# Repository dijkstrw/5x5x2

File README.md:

5x5x2 aka Orochi!
=================

This is a 5x5 Cherry mx matrix with hotswap Kailh sockets based my own
firmware for the STM32F1 with libopencm3. The project contains
firmware, schematics and a board layout in kicad.

Features you expect given the above picture:
- bios boot and nkro keyboards, using usb keyboard scancodes
- system and consumer codes
- mouse events
- usb serial interface for configuration
- 8 sk68xx background leds on the bottom board
- 25 sk68xx underglow leds on the top board
- rotary encoder

Advanced features:
- adjustable speed macrokeys to e.g. emit passwords
- all leds individually addressable, colorchord support
- leds can light on e.g. volume or desktop changes
- configuration can be adjusted and flashed in userflash
- and an automouse that can simulate fast clicking

More pictures of the board and the development dongle are
[here](docs/IMAGES.md). If you want to build this yourself see
[building](docs/BUILDING.md). Interactive bom is
[here](https://glcdn.githack.com/dijkstrw/5x5x2/-/raw/30abe2597a5d5bfca67bad37a444652a956d1f03/schematic/bom/ibom.html).

Default firmware / my usecase
-----------------------------

This is my macropad; it contains three layers:

- X workspace layer, select workspace number, move about in VLC, start
  apps, compose key, quick jump to password layer and a number of app
  starting keys. Rotary dial controls system volume. Rotary press
  mutes/unmutes.

  Rgbleds show sound volume, current workspace / screen and active
  layer.

- numeric keypad, for when tkl is not enough

- macrokeys layer

Features
========

Keyboards
---------

The board provides 3 types of keyboards via different usb
endpoints.

1. The first is the usb standard bios keyboard definition, which
   allows the keyboard also to emit key codes to hosts with limited
   usb hid support. (This used to be the case in <2015 style bioses,
   hence the name.)

2. The second keyboard is a n-key-rollover, which exposes a keyboard
   that allows 224 usb keyboard scancodes to be pressed
   simultaneously. Also, because we do not need to adhere to the bios
   boot standard, this endpoint's interval can set much lower = it
   types much faster.

3. The third keyboard can emit so called consumer and system
   codes. Example consumer key codes are PLAY, PAUSE, but also MARK,
   CLEARMARK, REPEATFROMMARK. So everything the typical multimedia
   keys emit and then some.

Mouse
-----

Operate the rodent from your keyboard! There is support for x, y, 5
buttons and a vertical and horizontal scrollwheel action.

Serial
------

The board exposes a serial port for logging and
configuration. Configuration is done using commands, with these
general rules:

- Commands with lowercase letters request configuration information

- Commands with capital letters set configuration

- Arguments often are two hexadecimal digits long; e.g. ``00``,
  ``12``, ``fa``. If more digits are required, this is denoted in the
  argument specification by a colon, like so ``<argument:4>``.

The available commands are:

    ?  - show a terse description of available commands.

    i  - show usb info strings; contains the git-describe tag of the
         current firmware.

    d  - dump configuration of a named subsystem, see below.
    dg - dump the keymap light group
    dk - dump the keymap
    dp - dump the palette
    dr - dump the rotary configuration

    B  - set the bottom set of 8 leds (backlight) to custom rgb values.
         Takes a RGB argument of the form <rgb:6> times 8 for all leds.

    C  - set the top set of 25 leds (frontlight) to custom rgb values.
         Takes a RGB argument of the form <rgb:6> times 25 for all leds.

    D  - tell keyboard about an event that can be translated into a rgb
         light event, see below.
    DD - <screen><display> set current desktop display
    DM - <mute>            set sound output mute status
    DR - <mute>            set sound input/record mute
    DV - <volume:4>        set sound volume
         See config directory for a program that emits these events to the
         keyboard.

    G  - set light map for a key, takes argument of the form
         <layer><row><column><value>

    I  - set the rgb light intensity.

    K  - redefine a key in the keymap, takes argument of the form
         <layer><row><column><type><arg1><arg2><arg3>

    A  - clear all macro keys.

    M  - define one macro key, takes an argument of the form
         <number><oftenusedstring>. The number is a two hexdigits, the
         string can be upto 32 7-bit ascii chars long and is terminated
         with a newline.

    N  - set keyboard mode to <argument>; 00 for bios and 01 for nkro.
         Default is bios.

    P  - set palette color, takes arguments
         <number><hue:4><saturation><value>

    R  - redefine the rotary command, takes a argument of
         the form <layer><direction><type><arg1><arg2><arg3>

    L  - load configuration from flash

    S  - save configuration to flash

    Z  - clear the configration flash, revert to "factory" keymap at
         next powerup.

Command interpretation starts after receiving a newline.

Light events
------------

The keyboard will show desktop events as rgbled changes. This works in
a number of steps:

- There is a host program that connects to the serial port, monitors
  sound and workspace changes and communicates that back to the
  keyboard. The program can be found in
  [susanoo.py](config/susanoo.py). Note that workspace changes sent
  via a fifo using the desktop manager and
  [configuration](config/keys_orochi.lua).

- Incoming events are mapped to be shown on particular leds using the
  lightmap command.

- The events all have their own displays:

         B - backlight    - slow rainbow easing
         D - desktop      - desktop display mapped over palette
         L - layer        - layer mapped over palette
         m - macro        - if macro active, else backlight
         M - sound mute   - different colors for mute status
         V - volume       - volume mapped to color

Palette
-------

Colors in easings are assigned using a color index in the palette. The
default palette strives for a selection of colors that are visually
distinct from another.

The rotary action forward, backward and backlight colors have fixed
indexes, and can be set by adjusting their assigned palette colors.

Automouse
---------

Automouse is a mouse clicker, with optional speed setting and wiggle
amounts. This allows you to click real fast, and wiggle the mouse
while using your hands for something else.

Macros
------

Macros set via serial are lost at power off unless the configuration
is written to flash. Loading from flash happens automatically at
powerup.

The strings that you provide via serial need to be translated into usb
keycodes, so currently only 7-bit ascii strings are supported.

Setting macros via the shell is easy:

    echo -e "\nM01Nevergonnagiveyouup!\n" > /dev/ttyACM0

Or see [set_macro.sh](util/set_macro.sh).

Notes:

- The initial newline is a trick to make sure our M will be considered
  the start of a command, no matter what has been put to the serial
  before by you, some driver or the os.
- This particular example defines the macro for macro key number 1.
- You need to have a macro key 1 in your keymap, otherwise you have
  nothing to trigger the macro.
- There is intentionally no way to display stored macros.

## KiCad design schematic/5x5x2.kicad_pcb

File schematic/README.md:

Other keyboard projects of interest:

- foostan: corne / crkb: the first time I saw sk6812 in mini-e
  variant. 
  
  https://github.com/foostan/kbd
  https://github.com/foostan/crkbd
  
  MIT license, parts reused:
  - Source of YS-SK6812-MINI-E schematic symbol, and 3d step model.

- KarlK90: Yaemk: indication that usb-c receptacle is usable without
  usb power negotiation.
  
  https://github.com/KarlK90/yaemk-split-kb
  
  GPLv3, used for inspiration only.

- Stefan Hamminga: sk6812mini model that models the underside of the
  package best.

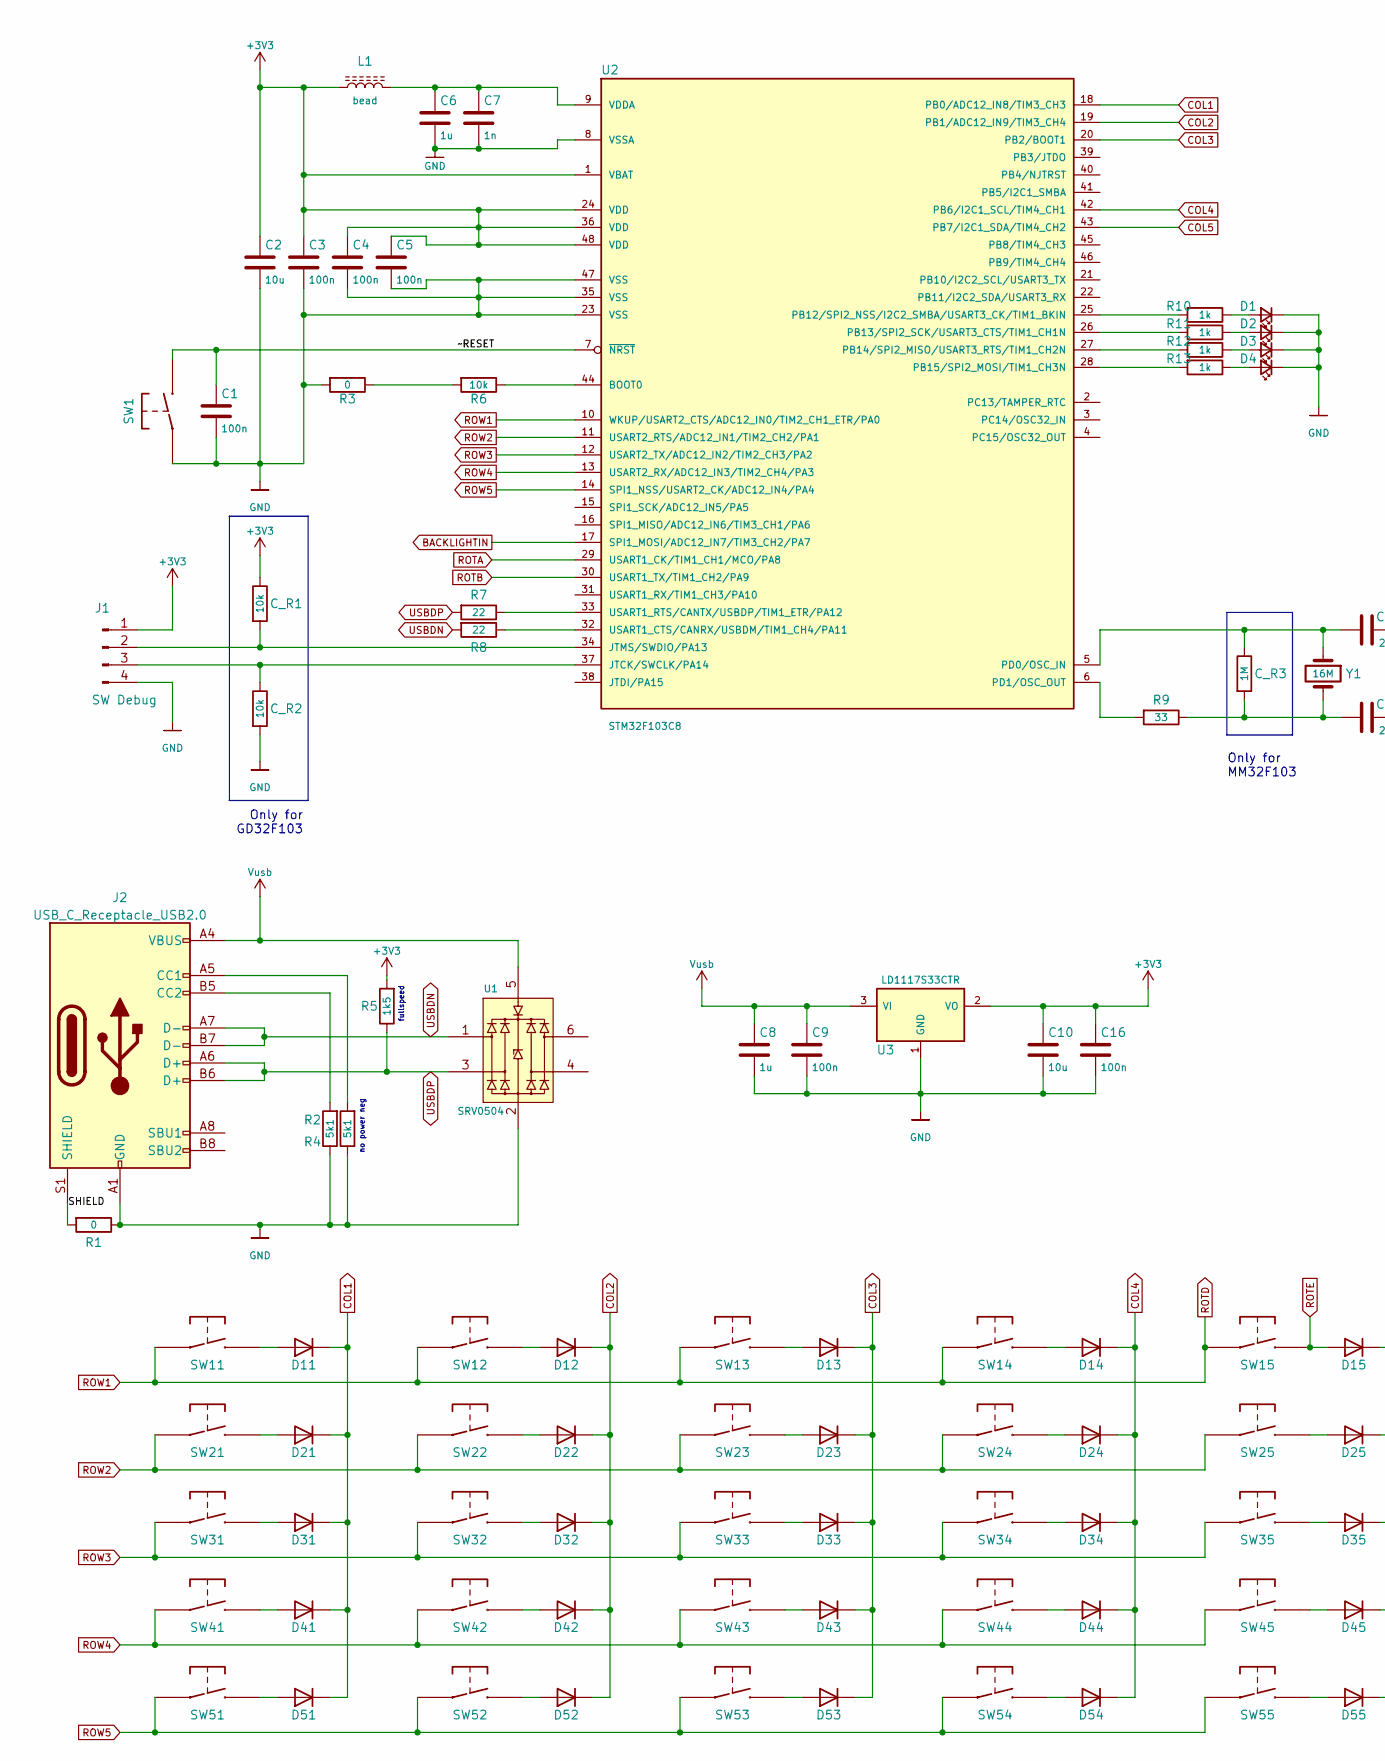
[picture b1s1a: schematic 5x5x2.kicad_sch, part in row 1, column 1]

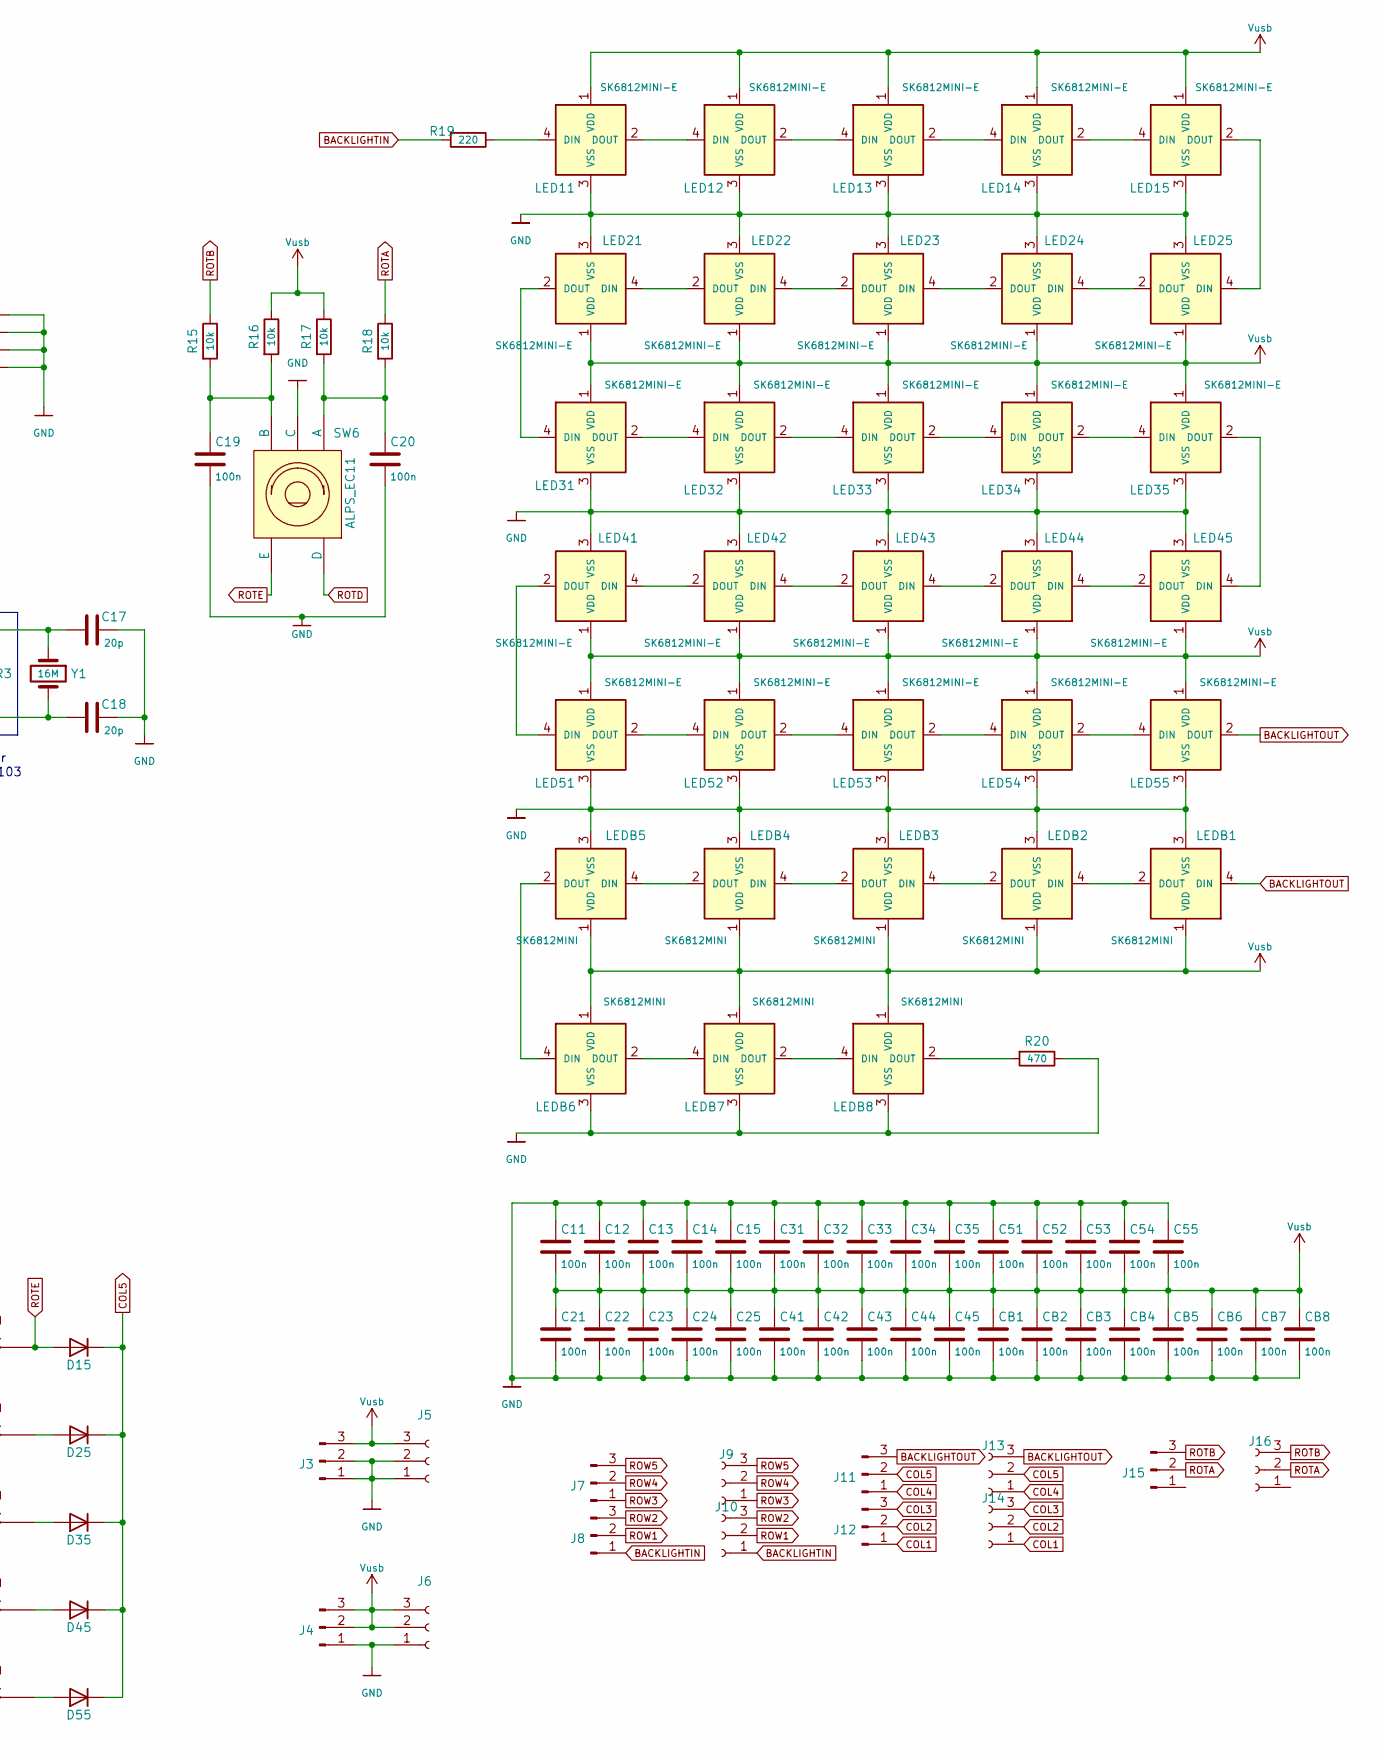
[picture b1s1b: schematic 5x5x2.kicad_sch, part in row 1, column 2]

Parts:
C1, C3, C4, C5, C9, C11, C12, C13, C14, C15, C16, C19, C20, C21, C22, C23, C24, C25, C31, C32, C33, C34, C35, C41, C42, C43, C44, C45, C51, C52, C53, C54, C55: 100n; C_0805_2012Metric
C2, C10: 10u; C_1206_3216Metric
C6, C8: 1u; C_1206_3216Metric
C7: 1n; C_0805_2012Metric
C17, C18: 20p; C_0805_2012Metric
CB1, CB2, CB3, CB4, CB5, CB6, CB7, CB8: 100n; C_0805_2012Metric
C_R1, C_R2: 10k; R_0805_2012Metric
C_R3: 1M; R_0805_2012Metric
D1, D2, D3, D4: Led_Small; LED_0805_2012Metric
D11, D12, D13, D14, D15, D21, D22, D23, D24, D25, D31, D32, D33, D34, D35, D41, D42, D43, D44, D45, D51, D52, D53, D54, D55: 1N4148; D_SOD-123F
J1: SW Debug; PinSocket_1x04_P2.54mm_Vertical
J2: USB_C_Receptacle_USB2.0; USB-C-SMD_TYPE-C-USB-4
J3, J4, J7, J8, J11, J12, J15: Conn_01x03_Male; PinSocket_1x03_P2.54mm_Vertical
J5, J6, J9, J10, J13, J14, J16: Conn_01x03_Female; PinSocket_1x03_P2.54mm_Vertical
L1: bead; C_0805_2012Metric
LED11, LED12, LED13, LED14, LED15, LED21, LED22, LED23, LED24, LED25, LED31, LED32, LED33, LED34, LED35, LED41, LED42, LED43, LED44, LED45, LED51, LED52, LED53, LED54, LED55: SK6812MINI-E; YS-SK6812MINI-E
LEDB1, LEDB2, LEDB3, LEDB4, LEDB5, LEDB6, LEDB7, LEDB8: SK6812MINI; SK6812MINI_rev
R1, R3: 0; R_0805_2012Metric
R2, R4: 5k1; R_0805_2012Metric
R5: 1k5; R_0805_2012Metric
R6, R15, R16, R17, R18: 10k; R_0805_2012Metric
R7, R8: 22; R_0805_2012Metric
R9: 33; R_0805_2012Metric
R10, R11, R12, R13: 1k; R_0805_2012Metric
R19: 220; R_0805_2012Metric
R20: 470; R_0805_2012Metric
SW1: SW; SW_SPST_FSMSM
SW6: ALPS_EC11; SW-TH_EC11XXXXXXXX
SW11, SW12, SW13, SW14, SW15, SW21, SW22, SW23, SW24, SW25, SW31, SW32, SW33, SW34, SW35, SW41, SW42, SW43, SW44, SW45, SW51, SW52, SW53, SW54, SW55: SW; SW_Hotswap_Kailh_MX_1.00u
U1: SRV0504; SOT-23-6_L2.9-W1.6-P0.95-LS2.8-BL
U2: STM32F103C8; LQFP-48_L7.0-W7.0-P0.50-LS9.0-BL
U3: LD1117S33CTR; SOT-223-4_L6.5-W3.5-P2.30-LS7.0-BR
Y1: 16M; Crystal_HC49-U_Vertical

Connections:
+3V3: C2.1, C3.1, C4.1, C5.1, C10.1, C16.1, C_R1.1, J1.1, L1.1, R5.2, U2.1 (VBAT), U2.24 (VDD), U2.36 (VDD), U2.48 (VDD), U3.2 (VO)
/SHIELD: J2.S1 (SHIELD), R1.2
/~RESET: C1.1, SW1.2, U2.7 (~NRST)
BACKLIGHTIN: J8.1, J10.1, R19.2, U2.17 (SPI1_MOSI/ADC12_IN7/TIM3_CH2/PA7)
BACKLIGHTOUT: J11.3, J13.3, LED55.2 (DOUT), LEDB1.4 (DIN)
COL1: D11.1 (K), D21.1 (K), D31.1 (K), D41.1 (K), D51.1 (K), J12.1, J14.1, U2.18 (PB0/ADC12_IN8/TIM3_CH3)
COL2: D12.1 (K), D22.1 (K), D32.1 (K), D42.1 (K), D52.1 (K), J12.2, J14.2, U2.19 (PB1/ADC12_IN9/TIM3_CH4)
COL3: D13.1 (K), D23.1 (K), D33.1 (K), D43.1 (K), D53.1 (K), J12.3, J14.3, U2.20 (PB2/BOOT1)
COL4: D14.1 (K), D24.1 (K), D34.1 (K), D44.1 (K), D54.1 (K), J11.1, J13.1, U2.42 (PB6/I2C1_SCL/TIM4_CH1)
COL5: D15.1 (K), D25.1 (K), D35.1 (K), D45.1 (K), D55.1 (K), J11.2, J13.2, U2.43 (PB7/I2C1_SDA/TIM4_CH2)
GND: C1.2, C2.2, C3.2, C4.2, C5.2, C6.2, C7.2, C8.2, C9.2, C10.2, C11.1, C12.1, C13.1, C14.1, C15.1, C16.2, C17.1, C18.1, C19.2, C20.2, C21.2, C22.2, C23.2, C24.2, C25.2, C31.1, C32.1, C33.1, C34.1, C35.1, C41.2, C42.2, C43.2, C44.2, C45.2, C51.1, C52.1, C53.1, C54.1, C55.1, CB1.2, CB2.2, CB3.2, CB4.2, CB5.2, CB6.2, CB7.2, CB8.2, C_R2.2, D1.1 (K), D2.1 (K), D3.1 (K), D4.1 (K), J1.4, J2.A1 (GND), J2.A12 (GND), J2.B1 (GND), J2.B12 (GND), J3.1, J3.2, J4.1, J5.1, J5.2, J6.1, LED11.3 (VSS), LED12.3 (VSS), LED13.3 (VSS), LED14.3 (VSS), LED15.3 (VSS), LED21.3 (VSS), LED22.3 (VSS), LED23.3 (VSS), LED24.3 (VSS), LED25.3 (VSS), LED31.3 (VSS), LED32.3 (VSS), LED33.3 (VSS), LED34.3 (VSS), LED35.3 (VSS), LED41.3 (VSS), LED42.3 (VSS), LED43.3 (VSS), LED44.3 (VSS), LED45.3 (VSS), LED51.3 (VSS), LED52.3 (VSS), LED53.3 (VSS), LED54.3 (VSS), LED55.3 (VSS), LEDB1.3 (VSS), LEDB2.3 (VSS), LEDB3.3 (VSS), LEDB4.3 (VSS), LEDB5.3 (VSS), LEDB6.3 (VSS), LEDB7.3 (VSS), LEDB8.3 (VSS), R1.1, R2.1, R3.2, R4.1, R20.1, SW1.1, SW6.C, U1.2 (GND), U2.8 (VSSA), U2.23 (VSS), U2.35 (VSS), U2.47 (VSS), U3.1 (GND)
unnamed: C6.1, C7.1, L1.2, U2.9 (VDDA)
unnamed: C17.2, C_R3.1, U2.5 (PD0/OSC_IN), Y1.1
unnamed: C18.2, C_R3.2, R9.1, Y1.2
unnamed: C19.1, R15.2, R16.2, SW6.B
unnamed: C20.1, R17.2, R18.2, SW6.A
unnamed: C_R1.2, J1.2, U2.34 (JTMS/SWDIO/PA13)
unnamed: C_R2.1, J1.3, U2.37 (JTCK/SWCLK/PA14)
unnamed: D1.2 (A), R10.1
unnamed: D2.2 (A), R11.1
unnamed: D3.2 (A), R12.1
unnamed: D4.2 (A), R13.1
unnamed: D11.2 (A), SW11.2
unnamed: D12.2 (A), SW12.2
unnamed: D13.2 (A), SW13.2
unnamed: D14.2 (A), SW14.2
unnamed: D21.2 (A), SW21.2
unnamed: D22.2 (A), SW22.2
unnamed: D23.2 (A), SW23.2
unnamed: D24.2 (A), SW24.2
unnamed: D25.2 (A), SW25.2
unnamed: D31.2 (A), SW31.2
unnamed: D32.2 (A), SW32.2
unnamed: D33.2 (A), SW33.2
unnamed: D34.2 (A), SW34.2
unnamed: D35.2 (A), SW35.2
unnamed: D41.2 (A), SW41.2
unnamed: D42.2 (A), SW42.2
unnamed: D43.2 (A), SW43.2
unnamed: D44.2 (A), SW44.2
unnamed: D45.2 (A), SW45.2
unnamed: D51.2 (A), SW51.2
unnamed: D52.2 (A), SW52.2
unnamed: D53.2 (A), SW53.2
unnamed: D54.2 (A), SW54.2
unnamed: D55.2 (A), SW55.2
unnamed: J2.A5 (CC1), R4.2
unnamed: J2.B5 (CC2), R2.2
unnamed: LED11.2 (DOUT), LED12.4 (DIN)
unnamed: LED11.4 (DIN), R19.1
unnamed: LED12.2 (DOUT), LED13.4 (DIN)
unnamed: LED13.2 (DOUT), LED14.4 (DIN)
unnamed: LED14.2 (DOUT), LED15.4 (DIN)
unnamed: LED15.2 (DOUT), LED25.4 (DIN)
unnamed: LED21.2 (DOUT), LED31.4 (DIN)
unnamed: LED21.4 (DIN), LED22.2 (DOUT)
unnamed: LED22.4 (DIN), LED23.2 (DOUT)
unnamed: LED23.4 (DIN), LED24.2 (DOUT)
unnamed: LED24.4 (DIN), LED25.2 (DOUT)
unnamed: LED31.2 (DOUT), LED32.4 (DIN)
unnamed: LED32.2 (DOUT), LED33.4 (DIN)
unnamed: LED33.2 (DOUT), LED34.4 (DIN)
unnamed: LED34.2 (DOUT), LED35.4 (DIN)
unnamed: LED35.2 (DOUT), LED45.4 (DIN)
unnamed: LED41.2 (DOUT), LED51.4 (DIN)
unnamed: LED41.4 (DIN), LED42.2 (DOUT)
unnamed: LED42.4 (DIN), LED43.2 (DOUT)
unnamed: LED43.4 (DIN), LED44.2 (DOUT)
unnamed: LED44.4 (DIN), LED45.2 (DOUT)
unnamed: LED51.2 (DOUT), LED52.4 (DIN)
unnamed: LED52.2 (DOUT), LED53.4 (DIN)
unnamed: LED53.2 (DOUT), LED54.4 (DIN)
unnamed: LED54.2 (DOUT), LED55.4 (DIN)
unnamed: LEDB1.2 (DOUT), LEDB2.4 (DIN)
unnamed: LEDB2.2 (DOUT), LEDB3.4 (DIN)
unnamed: LEDB3.2 (DOUT), LEDB4.4 (DIN)
unnamed: LEDB4.2 (DOUT), LEDB5.4 (DIN)
unnamed: LEDB5.2 (DOUT), LEDB6.4 (DIN)
unnamed: LEDB6.2 (DOUT), LEDB7.4 (DIN)
unnamed: LEDB7.2 (DOUT), LEDB8.4 (DIN)
unnamed: LEDB8.2 (DOUT), R20.2
unnamed: R3.1, R6.2
unnamed: R6.1, U2.44 (BOOT0)
unnamed: R7.1, U2.33 (USART1_RTS/CANTX/USBDP/TIM1_ETR/PA12)
unnamed: R8.1, U2.32 (USART1_CTS/CANRX/USBDM/TIM1_CH4/PA11)
unnamed: R9.2, U2.6 (PD1/OSC_OUT)
unnamed: R10.2, U2.25 (PB12/SPI2_NSS/I2C2_SMBA/USART3_CK/TIM1_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)
unnamed: R11.2, U2.26 (PB13/SPI2_SCK/USART3_CTS/TIM1_CH1N)
unnamed: R12.2, U2.27 (PB14/SPI2_MISO/USART3_RTS/TIM1_CH2N)
unnamed: R13.2, U2.28 (PB15/SPI2_MOSI/TIM1_CH3N)
ROTA: J15.2, J16.2, R18.1, U2.29 (USART1_CK/TIM1_CH1/MCO/PA8)
ROTB: J15.3, J16.3, R15.1, U2.30 (USART1_TX/TIM1_CH2/PA9)
ROTD: J8.2, J10.2, SW6.D, SW11.1, SW12.1, SW13.1, SW14.1, SW15.1, U2.10 (WKUP/USART2_CTS/ADC12_IN0/TIM2_CH1_ETR/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)
ROTE: D15.2 (A), SW6.E, SW15.2
ROW2: J8.3, J10.3, SW21.1, SW22.1, SW23.1, SW24.1, SW25.1, U2.11 (USART2_RTS/ADC12_IN1/TIM2_CH2/PA1)
ROW3: J7.1, J9.1, SW31.1, SW32.1, SW33.1, SW34.1, SW35.1, U2.12 (USART2_TX/ADC12_IN2/TIM2_CH3/PA2)
ROW4: J7.2, J9.2, SW41.1, SW42.1, SW43.1, SW44.1, SW45.1, U2.13 (USART2_RX/ADC12_IN3/TIM2_CH4/PA3)
ROW5: J7.3, J9.3, SW51.1, SW52.1, SW53.1, SW54.1, SW55.1, U2.14 (SPI1_NSS/USART2_CK/ADC12_IN4/PA4)
USBDN: J2.A7 (D-), J2.B7 (D-), R8.2, U1.1 (IO1)
USBDP: J2.A6 (D+), J2.B6 (D+), R5.1, R7.2, U1.3 (IO3)
Vusb: C8.1, C9.1, C11.2, C12.2, C13.2, C14.2, C15.2, C21.1, C22.1, C23.1, C24.1, C25.1, C31.2, C32.2, C33.2, C34.2, C35.2, C41.1, C42.1, C43.1, C44.1, C45.1, C51.2, C52.2, C53.2, C54.2, C55.2, CB1.1, CB2.1, CB3.1, CB4.1, CB5.1, CB6.1, CB7.1, CB8.1, J2.A4 (VBUS), J2.A9 (VBUS), J2.B4 (VBUS), J2.B9 (VBUS), J3.3, J4.2, J4.3, J5.3, J6.2, J6.3, LED11.1 (VDD), LED12.1 (VDD), LED13.1 (VDD), LED14.1 (VDD), LED15.1 (VDD), LED21.1 (VDD), LED22.1 (VDD), LED23.1 (VDD), LED24.1 (VDD), LED25.1 (VDD), LED31.1 (VDD), LED32.1 (VDD), LED33.1 (VDD), LED34.1 (VDD), LED35.1 (VDD), LED41.1 (VDD), LED42.1 (VDD), LED43.1 (VDD), LED44.1 (VDD), LED45.1 (VDD), LED51.1 (VDD), LED52.1 (VDD), LED53.1 (VDD), LED54.1 (VDD), LED55.1 (VDD), LEDB1.1 (VDD), LEDB2.1 (VDD), LEDB3.1 (VDD), LEDB4.1 (VDD), LEDB5.1 (VDD), LEDB6.1 (VDD), LEDB7.1 (VDD), LEDB8.1 (VDD), R16.1, R17.1, U1.5 (VDD), U3.3 (VI)

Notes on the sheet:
fullspeed
Only for MM32F103
Only for GD32F103
no power neg

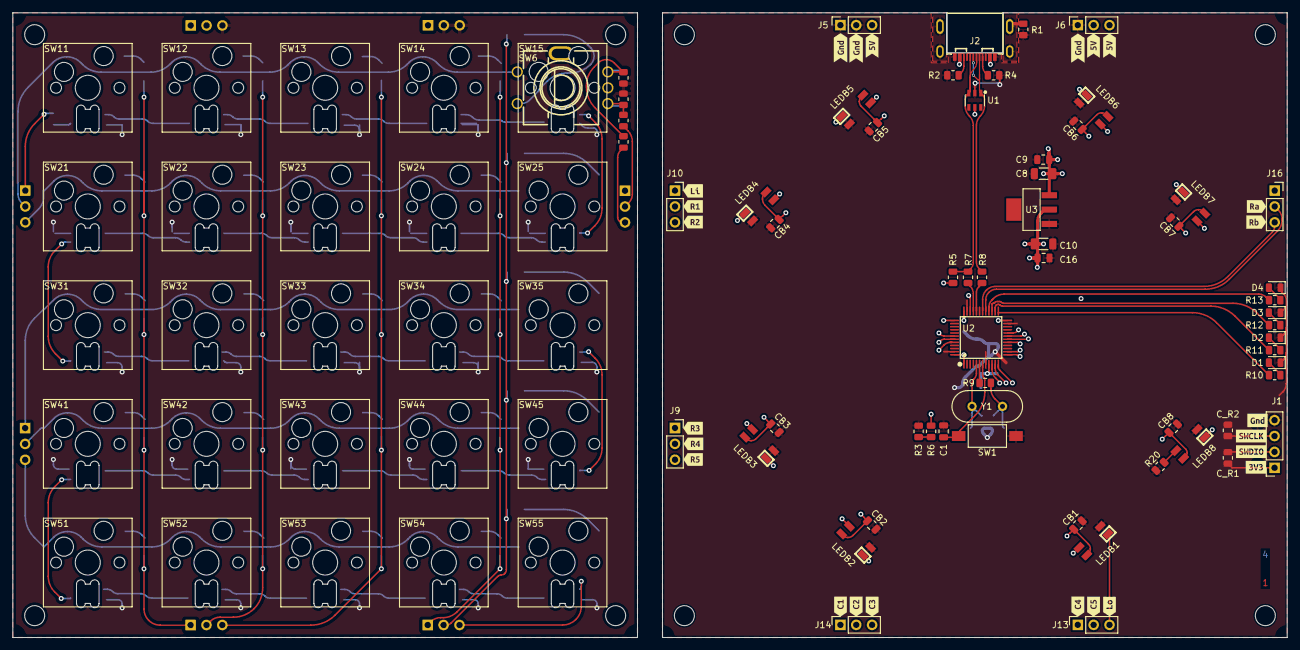
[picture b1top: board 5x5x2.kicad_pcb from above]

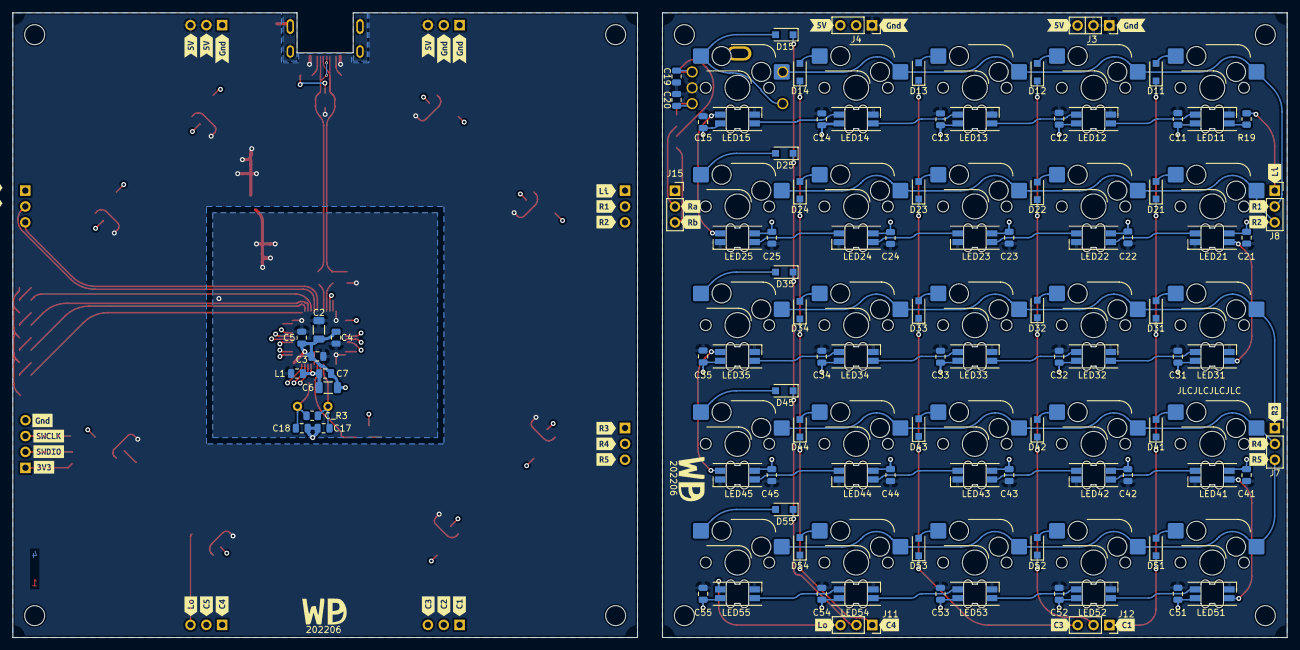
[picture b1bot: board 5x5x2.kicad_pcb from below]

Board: 4 copper layers, 204.0 x 100.0 mm, 244 parts (135 on the bottom side), 101 nets.

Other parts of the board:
kibuzzard-62AF6B0E: G***; kibuzzard-62AF6B0E
kibuzzard-62AF6B7C, kibuzzard-62AF6B7C#2: G***; kibuzzard-62AF6B7C
kibuzzard-62AF6B38, kibuzzard-62AF6B38#2: G***; kibuzzard-62AF6B38
kibuzzard-62AF6BA3, kibuzzard-62AF6BA3#2: G***; kibuzzard-62AF6BA3
kibuzzard-62AF6BAD, kibuzzard-62AF6BAD#2: G***; kibuzzard-62AF6BAD
kibuzzard-62AF6BF3: G***; kibuzzard-62AF6BF3
kibuzzard-62AF6D1E, kibuzzard-62AF6D1E#2: G***; kibuzzard-62AF6D1E
kibuzzard-62AF6DB1, kibuzzard-62AF6DB1#2: G***; kibuzzard-62AF6DB1
kibuzzard-62AF6E15: G***; kibuzzard-62AF6E15
kibuzzard-62AF6E21: G***; kibuzzard-62AF6E21
kibuzzard-62AF6EB6: G***; kibuzzard-62AF6EB6
kibuzzard-62AF6EDD: G***; kibuzzard-62AF6EDD
kibuzzard-62AF6F00: G***; kibuzzard-62AF6F00
kibuzzard-62AF6F11: G***; kibuzzard-62AF6F11
kibuzzard-62AF7A14, kibuzzard-62AF7A14#2: G***; kibuzzard-62AF7A14
kibuzzard-62AF7A28, kibuzzard-62AF7A28#2: G***; kibuzzard-62AF7A28
kibuzzard-62AF7A49, kibuzzard-62AF7A49#2: G***; kibuzzard-62AF7A49
kibuzzard-62AF7A56, kibuzzard-62AF7A56#2: G***; kibuzzard-62AF7A56
kibuzzard-62AF7CA9: G***; kibuzzard-62AF7CA9
kibuzzard-62AF7CCF: G***; kibuzzard-62AF7CCF
kibuzzard-62AF73B1, kibuzzard-62AF73B1#2, kibuzzard-62AF73B1#3, kibuzzard-62AF73B1#4, kibuzzard-62AF73B1#5, kibuzzard-62AF73B1#6: G***; kibuzzard-62AF73B1
kibuzzard-62AF73D1, kibuzzard-62AF73D1#2, kibuzzard-62AF73D1#3, kibuzzard-62AF73D1#4, kibuzzard-62AF73D1#5, kibuzzard-62AF73D1#6: G***; kibuzzard-62AF73D1
kibuzzard-62AF74B5, kibuzzard-62AF74B5#2: G***; kibuzzard-62AF74B5
kibuzzard-62AF74BF, kibuzzard-62AF74BF#2: G***; kibuzzard-62AF74BF
kibuzzard-62AF74C8, kibuzzard-62AF74C8#2: G***; kibuzzard-62AF74C8
kibuzzard-62AF74DA: G***; kibuzzard-62AF74DA
kibuzzard-62AF74E3: G***; kibuzzard-62AF74E3
kibuzzard-62AF74EC: G***; kibuzzard-62AF74EC
kibuzzard-62AF74F7: G***; kibuzzard-62AF74F7
kibuzzard-62AF74FE: G***; kibuzzard-62AF74FE
kibuzzard-62AF742E, kibuzzard-62AF742E#2: G***; kibuzzard-62AF742E
kibuzzard-62AF749F, kibuzzard-62AF749F#2: G***; kibuzzard-62AF749F
kibuzzard-62AF750A: G***; kibuzzard-62AF750A
kibuzzard-62AF7423, kibuzzard-62AF7423#2: G***; kibuzzard-62AF7423
kibuzzard-62AF7487, kibuzzard-62AF7487#2: G***; kibuzzard-62AF7487
kibuzzard-62AF7492, kibuzzard-62AF7492#2: G***; kibuzzard-62AF7492

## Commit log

2022-04-16 Added backlight using sk6812 leds
    The driver is in sk6812 and uses spi to communicate with a
    ledstrip. The mapping from rgb to spi format is hidden away in sk6812,
    and the backlight interactions will go to a dedicated own file.
2022-04-16 Rewrote bitbanding approach to get a tighter loop
    By separating the address and offset calculation when bitbanding, the
    compiler can now precompute the offsets, leading to a much tighter
    loop of just reading the current color bit and then writing that to
    the appropriate spi bit.
2022-04-17 Adjusted bit banding calculations to reflect ARM documentation
    The previous version included addition to uint32_t pointers. Addition
    of 1 then means add 4. Previously I had adjusted the defines to take
    the /4 into account, but then the calculations seem to diverge from
    what ARM specifies in their reference materials.
2022-04-18 SPI-DMA now runs contineously, while usb works on a bluepill
    Also: renamed to 5x5x2, and moved to a new git project directory.
2022-04-18 Started new schematic
2022-04-27 Added rotary encoder
    Also added optional components when using clones.
    Rotary encoder ideas and schematic symbol came from YAEMK -- check
    license if allowed, else redraw.
2022-04-29 Schematic now has usb-c, rotarty encoder and usb tvs protection.
2022-05-01 Added rotary encoder
    A rotary encoder can now be used to quickly emit events depending on
    rotation direction and current layer.
    The encoder is connected to timer 1 pins pa8 and pa9, and uses the
    quadriature decoding that is already available in the chip.
    Adjusted command.c to allow it to be set later on + adjusted flash
    load/save to be able to store the new settings.
2022-05-01 Add rotary encoder to pa8/pa9 on schematic
2022-05-14 Added initial hsv2rgb calculation for rainbow tests
    This helps determine that the leds are soldered right. Maybe include a
    rainbow in final keyboard also? That way we can check that everything
    works well at boot.
2022-05-17 Started assigning footprints
2022-05-22 Added footprints, started pcb
    - used easyeda converter to get lcsc parts
    - used the kicad standard addon kbd library for the kailh socket
    - used foostans sk6812
2022-05-27 Adjusted sk6812 footprint, started routing
    Adjusted sk6812 footprint from square cutout to something that is
    routable with a mill.
    The kailh sockets and leds eat up all the space between the keys. This
    means that there is not room for the micro, regulator and usb
    receptacle if we stay in a 10x10.
    Options:
2022-05-28 More routing
2022-06-03 Routed for mcu on other pcb
    This way we can stay with 2 layers, and optionally have an additional
    pcb for just the key switches without kailh holders.
2022-06-04 Added board interconnectors
    And started redoing the board interconnects -- the previous solution
    lacked symmetry and elegance (= looked like a dog's breakfast).
2022-06-06 Redid board connectors, started 2nd board
2022-06-18 Adjusted to 4 layer board
    - USB interface is most important, lets route that first.
    - leds interconnect will mess with everybody, so push those to the
    internal layer.
    - do away with quirky 45 degree placing
2022-06-19 Routed all remaining parts.
2022-06-19 Cleaned up silkscreen.
2022-06-25 Fixed up DRC, tested footprints.
2022-06-26 Filed for production;
    - added a silk voronoi on top of control board
    - adjusted wrong footprints for background leds
2022-07-10 Fix flash operations on GD32
    These devices have different internal flash and need two nops before
    flash is unlocked.
2022-07-10 Remove openocd, blackmagic via wlan is where its at
2022-07-10 Little documentation nits
2022-07-10 Add initial easing functions
2022-07-17 Moved to actual hardware
    - easing rainbow over the backlight leds to test them at boot
    - show usb enumeration on new 4 onboard leds
    - setup regview in default make debug
    - move leds to GPIOB
    - HSV now calculated via initializer
2022-07-30 Make two halves to get gerbers for 2 and 4 layer boards
    I will delete these derivatives after this commit.
2022-07-30 Dirty solution to the farthest keys not working
    A few of my keys do not register, yet do work when the oscilloscope is
    attached. I think the termination on the column lines is not
    ideal. Currently the nops are a dirty solution, I want to try to scan
    piecemail next.
2022-07-30 Now scan the matrix per row
    We now read the column input at the start of the matrix_scan function,
    and enable the next row at the end of this function. This allows the
    row signal to stabilise in between calls, and is more robust in the
    face of bad board layout.
    The function is more complex, as it can only build up an accurate
    picture of the keyboard after 5 consecutive calls. Update rate is
2022-07-31 Added new ease functions
    And I not really happy about it all -- the current crop have many
    magical numbers that I arrived at by trial and error.
2022-09-03 Bugfix: output at 2nd edge of sck
    This ensures that we comply closer to what the sk6812s are expecting,
    and my initial green led is now gone!
2022-09-11 Added backlight + rotation colors
    First step towards having an always on backlight + rotation that
    correlates to encoder movement
2022-10-02 Added rgb actions for key events
    This includes setting a group of keys to a color if a key is
    pressed. My usecase: I have a macropad that selects between 9
    workspaces. I want the workspace keys to have the color of the
    selected workspace. This way I have a visual reference of what
    workspace is selected at a glance.
2022-12-16 Nitpicking: use _t for types in rgbease
2022-12-23 Add first stab at layer movement
    The different ways to switch layers are:
    - MOVE - move to a particular layer using a keyboard switch
    - UP - move to higher layer
    - DOWN - move to lower layer
    - NEXTKEY - go to new layer for only next keypress
    - HOLD - while held goto layer, return on release
2022-12-23 Moved easing to use a palette of colors
    The easings now point to a color number in a palette. This way easing
    definitions take less space for later inclusion into userflash.
2022-12-24 Make palette, rgb ease and group set and save-able
2022-12-27 Add dump rotary
2022-12-27 Make dump statements uniform
2022-12-29 Nits: function definitions + sets check for bounds
2023-01-05 Adjusted footprints for easier soldering
    - sk6812mini-e slot was too large, results in non aligned parts
    - sk6812 pads were ideal for ovenized soldering, not so much for
    handwork.
2023-01-06 Allow direct modification of rgb leds via serial
2023-01-06 Assign background color from palette, cleanup palette
    Cleanup is to ensure that the colors in the palette a different enough
    to be recognizable when assigned to a key.
2023-01-07 Add backlight intensity
2023-01-07 Improve docker/dev.sh
    docker/dev.sh can now be called for an interactive shell, or be given
    args that will be executed in the docker and returned.
2023-01-07 Update README
    - add my usecase to explain where the weird easing, groups and
    palettes are for.
    - add palette
2023-01-08 Do not adjust easing of leds when set direct via serial
    - Also: make sure rgbintensity has a reasonable default
2023-01-08 Cleanup Makefile
2023-01-14 Improved layer handling
    - A layer key can modify the current layer, and with that make that a
    different key is reported at keyup. Now we detect this and send the
    keyup of the previous layer.
    - This requires that we use layer.c to tell us what key was
    pressed. The mechanics for <only layer change for next key> is easy to
    integrate there also.
2023-01-29 Keys in standard map are all reported in evdev/X
    This means that all keys generate keyboard events in my vanilla x
    environment, and can be bound right away using your window manager.
    (This removes the need to horse about with xkb to get all the key
    presses available in X, given that you can get then through evdev.)
2023-02-18 Update documentation
2023-02-18 Move misc docs to docs dir
2023-02-18 Fix set_macro.sh and mention in README
2023-08-25 Fix off by one bug for first backlight led
    It was set as > RGB_BACKLIGHT_OFFSET, it should be >=. This way leds
    25-32 get assigned backlight duty which is correct when viewing the
    number of led addresses as (25 + 8 - 1).
2023-11-10 Set compile flags + set make to docker/make using direnv
2023-12-09 Drop ease tied to a key, goto ease tied to an event
    I'd like to see the active desktop as a color under my 5x5x2. Make a
    way for my window manager to tell the keyboard where we are at.
    As a consequence I'm removing the ability to set colors to
    keypresses. I think that is too simple, we want colors on events. And
    while events can be keypresses, it can also be e.g. the host telling
    us what just happened.
2023-12-09 Add sound events
2023-12-10 Cleaning up sound events
    - mute state was confused with mic_mute
    - remove arbitrary const color defs in favour for declaring all our
    palette colors as const hsv_t
    - make instant jumps to color for sound operations
    - map volume to hue starting from yellow to red
2023-12-10 Add light layer events, init light at poweron
2023-12-16 Improve keymap - use keys that are accessible
    and not in the way of other uses. Also the keys chosen now are all
    within my xorg 0xff limit, so really usable without much trouble.
2023-12-16 Make sure rgbintensity is applied when setting colors
2023-12-16 Make light setting configurable via serial and flash
2023-12-16 Add host configuration details
2023-12-22 Fix flash writing
    Writing flash is tricky business;
    - We need to write out our data per 4 bytes, make sure our source data
    is aligned and padded to 4 bytes.
    - Pointer arithmetic is hard. (uint32_t)++ != (uint32_t *)++
    So:
    - Make sure to pad lightmap so that it is always modulo 4 = 0.
2023-12-22 Set background for front leds that want it
2023-12-26 Set macro light on front leds when macro is running
    Also:
    - set max brightness out of the box
    - add a contineous flashing color mode to indicate an ongoing activity
    At first I had removed the single-color led action that is also
    triggered on macro running, but if the user does not assign a frontend
    RGB led to 'MACRO' the discrete led is still useful.
2023-12-28 Add a slow rainbow as a background effect
    The default one color only light as backlight is not as pretty as
    unicorn colors moving slowly across the keyboard.
    This is a first stab; next step could be to allow the user to say
    background effect = fixed color, slow rainbow, pulsing color.
    Let's try to life with this for a few days first.
2023-12-28 Make sure rotary emits same keys in all layers
    Up/down orientation can change on the type of rotary encoder used:
    - ALPS: _K(VOL_DOWN), _K(VOL_UP)
    - BI Technologies EN11: _K(VOL_UP), _K(VOL_DOWN)
2023-12-30 Start of enclosure in openscad
2023-12-31 First top plate
    This is still not quite right, but a good first start. Inter spacing
    should be 5mm, for instance.
2024-01-02 Finished enclosure in OpenSCAD
2024-01-02 Show all tag switching on keyboard, also for single screen
2024-01-05 Document light map, update command and readme files
